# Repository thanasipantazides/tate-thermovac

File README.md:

# Tate 220 ThermoVac Chamber

Here lies a PCB design and code for instrumentation of the UMN Tate Hall rm 220 thermal-vacuum chamber.

The PCB design is in KiCad 10 format. There may be some custom footprint and symbol libraries missing from this distribution; I need to figure out how to bundle all this into the repository.

This board is supposed to read out ~17 NTC thermistors in the chamber, digitize them, and do something useful with the values. It also exposes some general-purpose ADC channels, an SPI, and a UART for peripheral communication. In addition to USB and Ethernet.

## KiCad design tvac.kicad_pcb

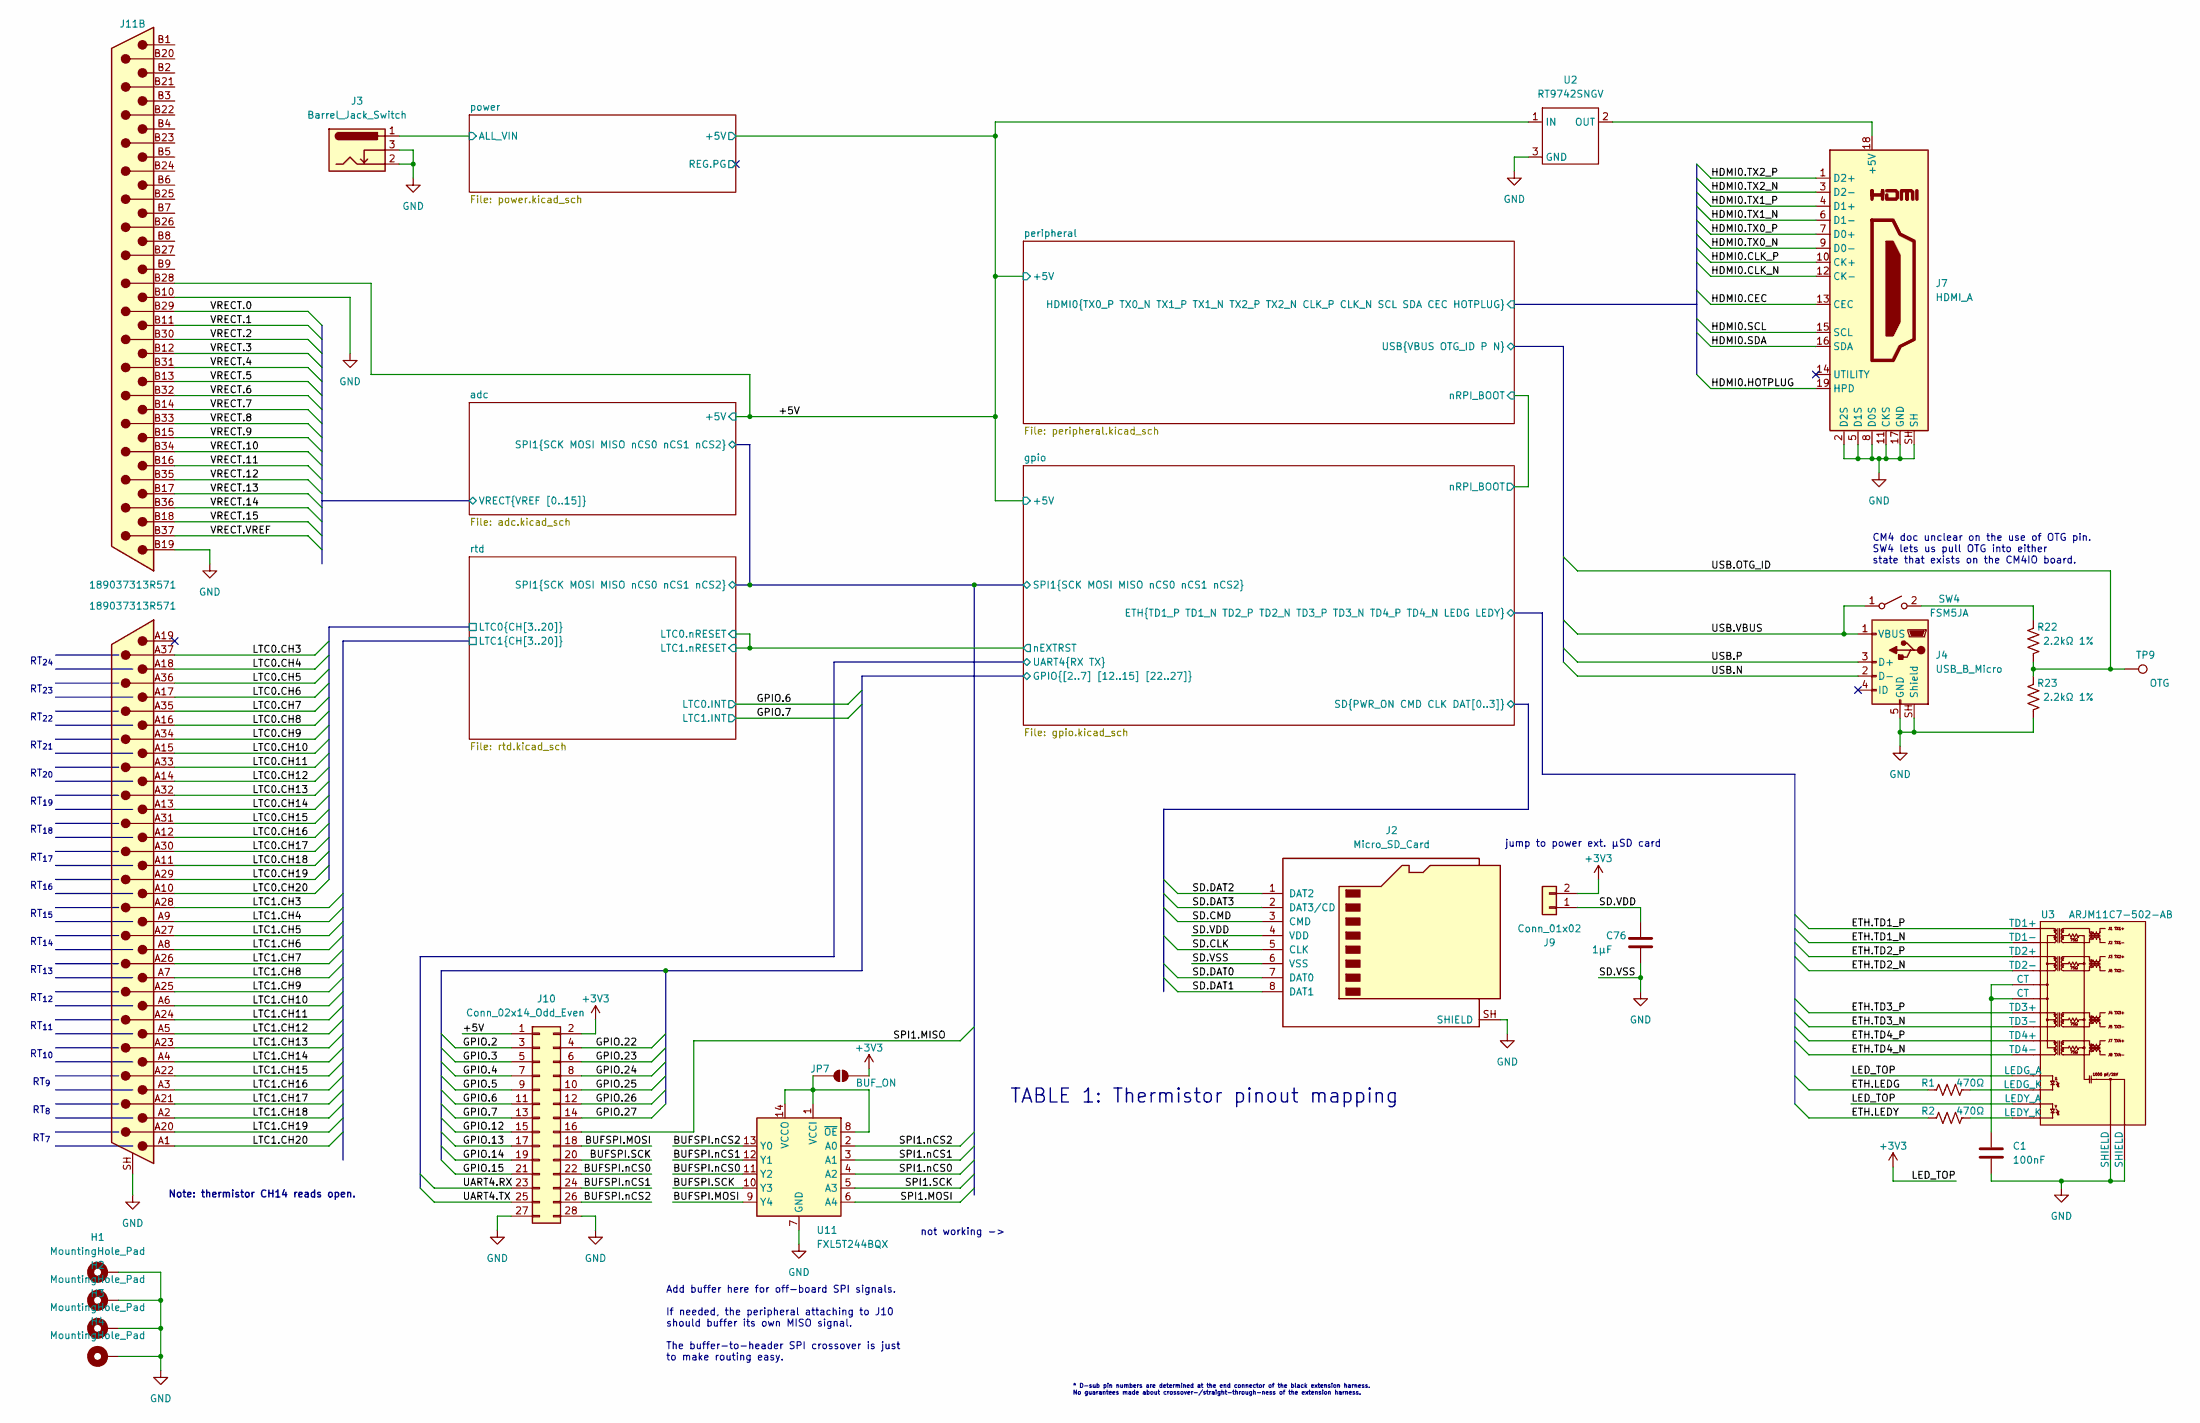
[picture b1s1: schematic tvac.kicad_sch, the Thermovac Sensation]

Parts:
C1: 100nF; C_0603_1608Metric
C76: 1µF; C_0603_1608Metric
H1, H2, H3, H4: MountingHole_Pad; MountingHole_4.3mm_M4_DIN965_Pad
J2: Micro_SD_Card; microSD_HC_Wuerth_693072010801
J3: Barrel_Jack_Switch; BarrelJack_Wuerth_6941xx301002; Digikey 732-5930-ND
J4: USB_B_Micro; USB_Micro-B_Amphenol_10118194-0001LF_Horizontal; Digikey 609-4618-1-ND
J7: HDMI_A; HDMI_A_Amphenol_10029449-x01xLF_Horizontal; Digikey 609-1010-1-ND
J9: Conn_01x02; PinHeader_1x02_P2.54mm_Vertical
J10: Conn_02x14_Odd_Even; PinHeader_2x14_P2.54mm_Vertical
J11: 189037313R571; DSUB-37-Stacked_NorComp-189037313R571
JP7: BUF_ON; SolderJumper-2_P1.3mm_Open_RoundedPad1.0x1.5mm
R1, R2: 470Ω; R_0603_1608Metric
R22, R23: 2.2kΩ 1%; R_0603_1608Metric
SW4: FSM5JA; SW_DIP_SPSTx01_Slide_9.78x4.72mm_W7.62mm_P2.54mm
TP9: OTG; TestPoint_Pad_D2.5mm
U2: RT9742SNGV; SOT-23-3
U3: ARJM11C7-502-AB; RJ45_Abracon_ARJM11C7-502-AB
U11: FXL5T244BQX; DHWQFN-14-1EP_2.5x3mm_P0.5mm_EP1x1.5mm

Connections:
+3V3: J9.2, J10.2, JP7.2 (B), U3.P11 (LEDG_A), U3.P13 (LEDY_A); also elsewhere on the board
/+5V: J10.1, J11.B28 (28), U2.1 (IN); also elsewhere on the board
/BUFSPI.MOSI: J10.18, U11.9 (Y4)
/BUFSPI.SCK: J10.20, U11.10 (Y3)
/BUFSPI.nCS0: J10.22, U11.11 (Y2)
/BUFSPI.nCS1: J10.24, U11.12 (Y1)
/BUFSPI.nCS2: J10.26, U11.13 (Y0)
/SD.VDD: C76.1, J2.4 (VDD), J9.1
/adc/SPI1.MISO: J10.16; also elsewhere on the board
/adc/SPI1.MOSI: U11.6 (A4); also elsewhere on the board
/adc/SPI1.SCK: U11.5 (A3); also elsewhere on the board
/adc/SPI1.nCS0: U11.4 (A2); also elsewhere on the board
/adc/SPI1.nCS1: U11.3 (A1); also elsewhere on the board
/adc/SPI1.nCS2: U11.2 (A0); also elsewhere on the board
/adc/VRECT.0: J11.B29 (29); also elsewhere on the board
/adc/VRECT.1: J11.B11 (11); also elsewhere on the board
/adc/VRECT.2: J11.B30 (30); also elsewhere on the board
/adc/VRECT.3: J11.B12 (12); also elsewhere on the board
/adc/VRECT.4: J11.B31 (31); also elsewhere on the board
/adc/VRECT.5: J11.B13 (13); also elsewhere on the board
/adc/VRECT.6: J11.B32 (32); also elsewhere on the board
/adc/VRECT.7: J11.B14 (14); also elsewhere on the board
/adc/VRECT.8: J11.B33 (33); also elsewhere on the board
/adc/VRECT.9: J11.B15 (15); also elsewhere on the board
/adc/VRECT.10: J11.B34 (34); also elsewhere on the board
/adc/VRECT.11: J11.B16 (16); also elsewhere on the board
/adc/VRECT.12: J11.B35 (35); also elsewhere on the board
/adc/VRECT.13: J11.B17 (17); also elsewhere on the board
/adc/VRECT.14: J11.B36 (36); also elsewhere on the board
/adc/VRECT.15: J11.B18 (18); also elsewhere on the board
/adc/VRECT.VREF: J11.B37 (37); also elsewhere on the board
/gpio/ETH.LEDG: R1.1; also elsewhere on the board
/gpio/ETH.LEDY: R2.1; also elsewhere on the board
/gpio/ETH.TD1_N: U3.P2 (TD1-); also elsewhere on the board
/gpio/ETH.TD1_P: U3.P1 (TD1+); also elsewhere on the board
/gpio/ETH.TD2_N: U3.P4 (TD2-); also elsewhere on the board
/gpio/ETH.TD2_P: U3.P3 (TD2+); also elsewhere on the board
/gpio/ETH.TD3_N: U3.P8 (TD3-); also elsewhere on the board
/gpio/ETH.TD3_P: U3.P7 (TD3+); also elsewhere on the board
/gpio/ETH.TD4_N: U3.P10 (TD4-); also elsewhere on the board
/gpio/ETH.TD4_P: U3.P9 (TD4+); also elsewhere on the board
/gpio/GPIO.2: J10.3; also elsewhere on the board
/gpio/GPIO.3: J10.5; also elsewhere on the board
/gpio/GPIO.4: J10.7; also elsewhere on the board
/gpio/GPIO.5: J10.9; also elsewhere on the board
/gpio/GPIO.6: J10.11; also elsewhere on the board
/gpio/GPIO.7: J10.13; also elsewhere on the board
/gpio/GPIO.12: J10.15; also elsewhere on the board
/gpio/GPIO.13: J10.17; also elsewhere on the board
/gpio/GPIO.14: J10.19; also elsewhere on the board
/gpio/GPIO.15: J10.21; also elsewhere on the board
/gpio/GPIO.22: J10.4; also elsewhere on the board
/gpio/GPIO.23: J10.6; also elsewhere on the board
/gpio/GPIO.24: J10.8; also elsewhere on the board
/gpio/GPIO.25: J10.10; also elsewhere on the board
/gpio/GPIO.26: J10.12; also elsewhere on the board
/gpio/GPIO.27: J10.14; also elsewhere on the board
/gpio/SD.CLK: J2.5 (CLK); also elsewhere on the board
/gpio/SD.CMD: J2.3 (CMD); also elsewhere on the board
/gpio/SD.DAT0: J2.7 (DAT0); also elsewhere on the board
/gpio/SD.DAT1: J2.8 (DAT1); also elsewhere on the board
/gpio/SD.DAT2: J2.1 (DAT2); also elsewhere on the board
/gpio/SD.DAT3: J2.2 (DAT3/CD); also elsewhere on the board
/gpio/UART4.RX: J10.23; also elsewhere on the board
/gpio/UART4.TX: J10.25; also elsewhere on the board
/peripheral/HDMI0.CEC: J7.13 (CEC); also elsewhere on the board
/peripheral/HDMI0.CLK_N: J7.12 (CK-); also elsewhere on the board
/peripheral/HDMI0.CLK_P: J7.10 (CK+); also elsewhere on the board
/peripheral/HDMI0.HOTPLUG: J7.19 (HPD); also elsewhere on the board
/peripheral/HDMI0.SCL: J7.15 (SCL); also elsewhere on the board
/peripheral/HDMI0.SDA: J7.16 (SDA); also elsewhere on the board
/peripheral/HDMI0.TX0_N: J7.9 (D0-); also elsewhere on the board
/peripheral/HDMI0.TX0_P: J7.7 (D0+); also elsewhere on the board
/peripheral/HDMI0.TX1_N: J7.6 (D1-); also elsewhere on the board
/peripheral/HDMI0.TX1_P: J7.4 (D1+); also elsewhere on the board
/peripheral/HDMI0.TX2_N: J7.3 (D2-); also elsewhere on the board
/peripheral/HDMI0.TX2_P: J7.1 (D2+); also elsewhere on the board
/peripheral/USB.N: J4.2 (D-); also elsewhere on the board
/peripheral/USB.OTG_ID: R22.2, R23.1, TP9.1 (1_1); also elsewhere on the board
/peripheral/USB.P: J4.3 (D+); also elsewhere on the board
/peripheral/USB.VBUS: J4.1 (VBUS), SW4.1 (A); also elsewhere on the board
/power/ALL_VIN: J3.1; also elsewhere on the board
/rtd/LTC0.CH4: J11.A18 (18); also elsewhere on the board
/rtd/LTC0.CH6: J11.A17 (17); also elsewhere on the board
/rtd/LTC0.CH8: J11.A16 (16); also elsewhere on the board
/rtd/LTC0.CH9: J11.A29 (29), J11.A30 (30), J11.A31 (31), J11.A32 (32), J11.A33 (33), J11.A34 (34), J11.A35 (35), J11.A36 (36), J11.A37 (37); also elsewhere on the board
/rtd/LTC0.CH10: J11.A15 (15); also elsewhere on the board
/rtd/LTC0.CH12: J11.A14 (14); also elsewhere on the board
/rtd/LTC0.CH14: J11.A13 (13); also elsewhere on the board
/rtd/LTC0.CH16: J11.A12 (12); also elsewhere on the board
/rtd/LTC0.CH18: J11.A11 (11); also elsewhere on the board
/rtd/LTC0.CH20: J11.A10 (10); also elsewhere on the board
/rtd/LTC1.CH4: J11.A9 (9); also elsewhere on the board
/rtd/LTC1.CH6: J11.A8 (8); also elsewhere on the board
/rtd/LTC1.CH8: J11.A7 (7); also elsewhere on the board
/rtd/LTC1.CH9: J11.A20 (20), J11.A21 (21), J11.A22 (22), J11.A23 (23), J11.A24 (24), J11.A25 (25), J11.A26 (26), J11.A27 (27), J11.A28 (28); also elsewhere on the board
/rtd/LTC1.CH10: J11.A6 (6); also elsewhere on the board
/rtd/LTC1.CH12: J11.A5 (5); also elsewhere on the board
/rtd/LTC1.CH14: J11.A4 (4); also elsewhere on the board
/rtd/LTC1.CH16: J11.A3 (3); also elsewhere on the board
/rtd/LTC1.CH18: J11.A2 (2); also elsewhere on the board
/rtd/LTC1.CH20: J11.A1 (1); also elsewhere on the board
GND: C1.2, C76.2, H1.1 (1_1), H2.1 (1_1), H3.1 (1_1), H4.1 (1_1), J2.6 (VSS), J2.SH (SHIELD), J3.2, J3.3, J4.5 (GND), J4.SH (Shield), J7.2 (D2S), J7.5 (D1S), J7.8 (D0S), J7.11 (CKS), J7.17 (GND), J7.SH, J10.27, J10.28, J11.B10 (10), J11.B19 (19), J11.SH (PAD), R23.2, U2.3 (GND), U3.H1 (SHIELD), U3.H2 (SHIELD), U11.7 (GND); also elsewhere on the board
unnamed: C1.1, U3.P5 (CT), U3.P6 (CT)
unnamed: J7.18 (+5V), U2.2 (OUT)
unnamed: JP7.1 (A), U11.1 (VCCI), U11.8 (~OE), U11.14 (VCCO)
unnamed: R22.1, SW4.2 (B)
unnamed: R1.2, U3.P12 (LEDG_K)
unnamed: R2.2, U3.P14 (LEDY_K)

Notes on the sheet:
RT_{8}
RT_{23}
jump to power ext. µSD card
RT_{12}
RT_{24}
RT_{17}
Note: thermistor CH14 reads open.
RT_{16}
RT_{11}
RT_{7}
RT_{20}
RT_{22}
TABLE 1: Thermistor pinout mapping
RT_{9}
RT_{13}
RT_{21}
RT_{19}
not working ->
* D-sub pin numbers are determined at the end connector of the black extension harness. No guarantees made about crossover-/straight-through-ness of the extension harness.
Add buffer here for off-board SPI signals. If needed, the peripheral attaching to J10 should buffer its own MISO signal. The buffer-to-header SPI crossover is just to make routing easy.
RT_{14}
RT_{18}
RT_{15}
CM4 doc unclear on the use of OTG pin. SW4 lets us pull OTG into either state that exists on the CM4IO board.
RT_{10}

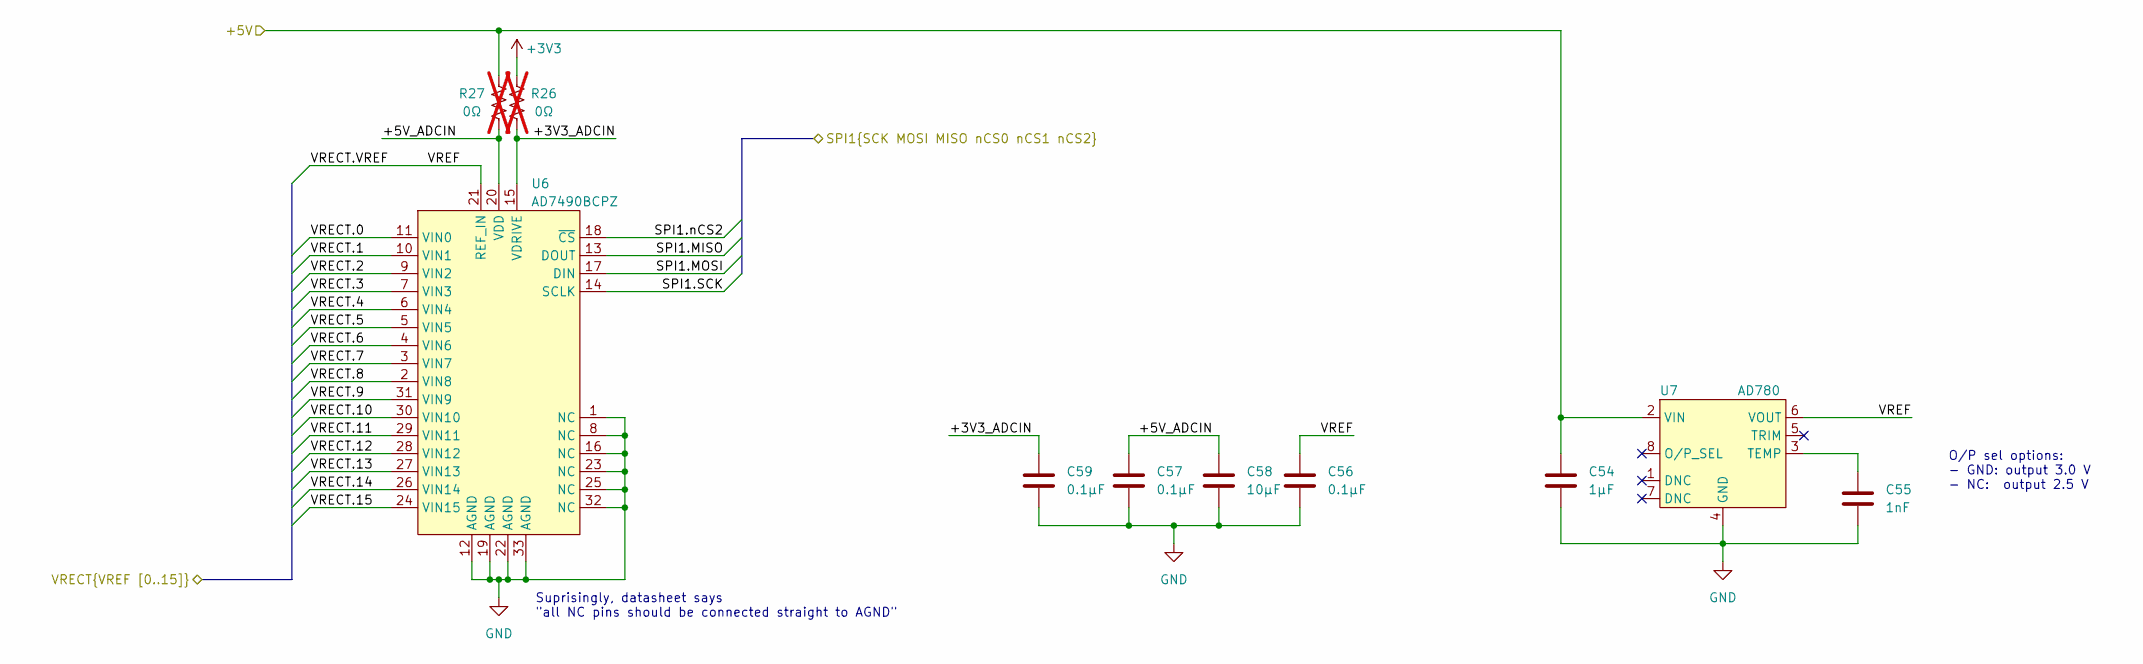
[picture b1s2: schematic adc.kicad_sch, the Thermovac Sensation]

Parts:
C54: 1µF; C_0603_1608Metric
C55: 1nF; C_0603_1608Metric
C56, C57, C59: 0.1µF; C_0603_1608Metric
C58: 10µF; C_1210_3225Metric
R26, R27: 0Ω; R_1210_3225Metric; not fitted
U6: AD7490BCPZ; LFCSP-32-1EP_5x5mm_P0.5mm_EP3.5x3.5mm; Digikey 505-AD7490BCPZ-ND
U7: AD780; SOIC-8_3.9x4.9mm_P1.27mm; Digikey 505-AD780ARZ-ND

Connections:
+3V3: R26.2; also elsewhere on the board
/+5V: C54.1, R27.2, U7.2 (VIN); also elsewhere on the board
/adc/+3V3_ADCIN: C59.1, R26.1, U6.15 (VDRIVE)
/adc/+5V_ADCIN: C57.1, C58.1, R27.1, U6.20 (VDD)
/adc/SPI1.MISO: U6.13 (DOUT); also elsewhere on the board
/adc/SPI1.MOSI: U6.17 (DIN); also elsewhere on the board
/adc/SPI1.SCK: U6.14 (SCLK); also elsewhere on the board
/adc/SPI1.nCS2: U6.18 (~CS); also elsewhere on the board
/adc/VRECT.0: U6.11 (VIN0); also elsewhere on the board
/adc/VRECT.1: U6.10 (VIN1); also elsewhere on the board
/adc/VRECT.2: U6.9 (VIN2); also elsewhere on the board
/adc/VRECT.3: U6.7 (VIN3); also elsewhere on the board
/adc/VRECT.4: U6.6 (VIN4); also elsewhere on the board
/adc/VRECT.5: U6.5 (VIN5); also elsewhere on the board
/adc/VRECT.6: U6.4 (VIN6); also elsewhere on the board
/adc/VRECT.7: U6.3 (VIN7); also elsewhere on the board
/adc/VRECT.8: U6.2 (VIN8); also elsewhere on the board
/adc/VRECT.9: U6.31 (VIN9); also elsewhere on the board
/adc/VRECT.10: U6.30 (VIN10); also elsewhere on the board
/adc/VRECT.11: U6.29 (VIN11); also elsewhere on the board
/adc/VRECT.12: U6.28 (VIN12); also elsewhere on the board
/adc/VRECT.13: U6.27 (VIN13); also elsewhere on the board
/adc/VRECT.14: U6.26 (VIN14); also elsewhere on the board
/adc/VRECT.15: U6.24 (VIN15); also elsewhere on the board
/adc/VRECT.VREF: C56.1, U6.21 (REF_IN), U7.6 (VOUT); also elsewhere on the board
GND: C54.2, C55.2, C56.2, C57.2, C58.2, C59.2, U6.1 (NC), U6.8 (NC), U6.12 (AGND), U6.16 (NC), U6.19 (AGND), U6.22 (AGND), U6.23 (NC), U6.25 (NC), U6.32 (NC), U6.33 (AGND), U7.4 (GND); also elsewhere on the board
unnamed: C55.1, U7.3 (TEMP)

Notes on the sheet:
O/P sel options: - GND: output 3.0 V - NC: output 2.5 V
Suprisingly, datasheet says "all NC pins should be connected straight to AGND"

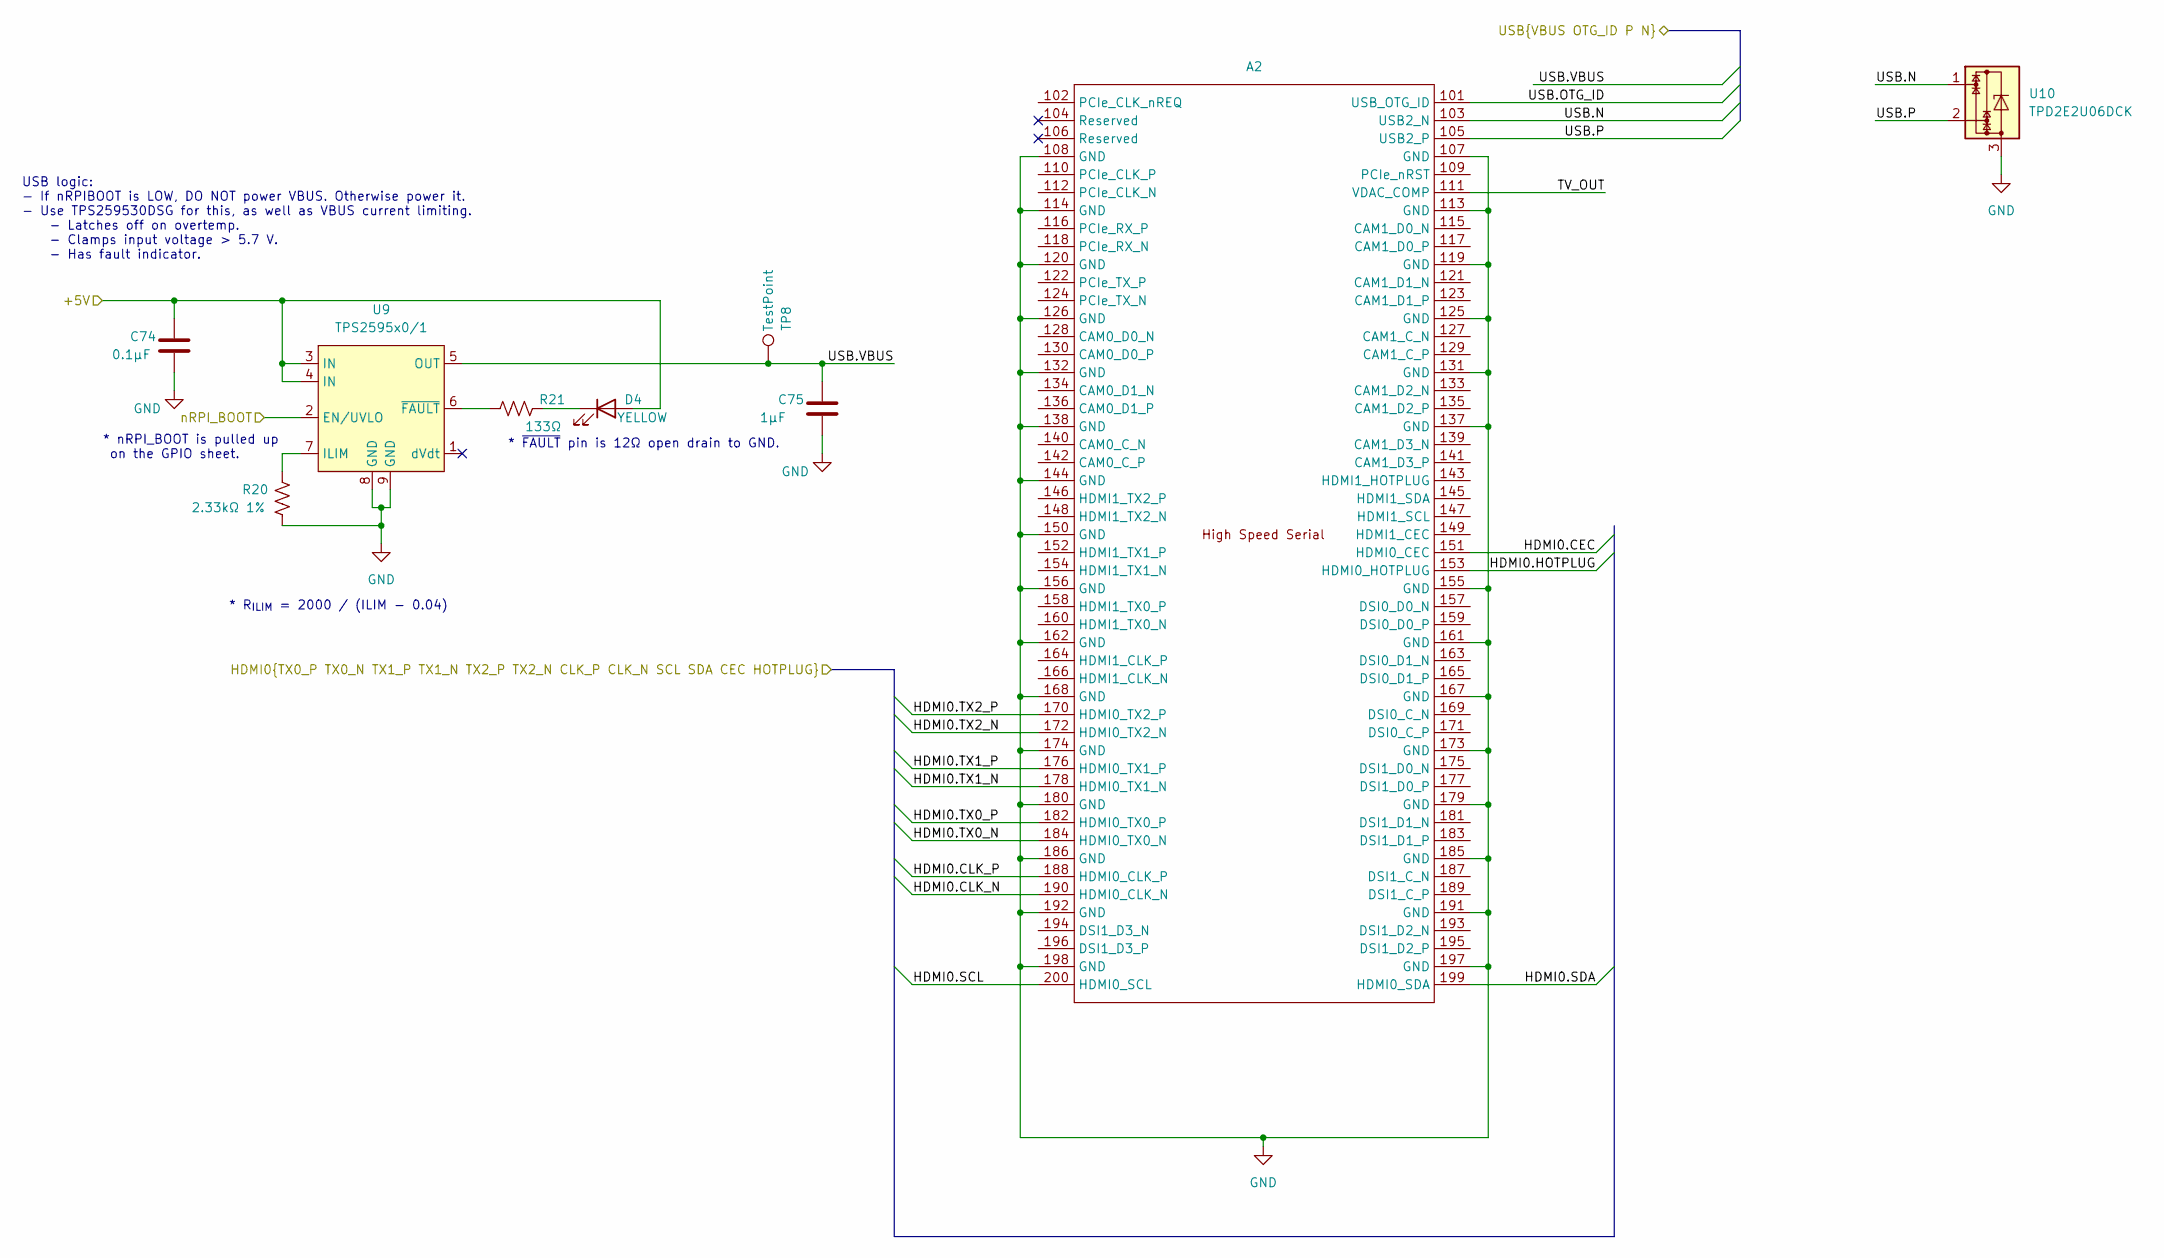
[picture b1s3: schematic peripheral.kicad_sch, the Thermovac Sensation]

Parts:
A2: Hirose_DF40HC(3.0)-100DS-0.4V_2x50_P0.4mm_RPi_CM4-BUS
C74: 0.1µF; C_0603_1608Metric
C75: 1µF; C_0603_1608Metric
D4: YELLOW; LED_1206_3216Metric; Digikey 160-1406-1-ND
R20: 2.33kΩ 1%; R_0603_1608Metric
R21: 133Ω; R_0603_1608Metric
TP8: TestPoint; TestPoint_Pad_D2.5mm
U9: TPS2595x0/1; WSON-8-1EP_2x2mm_P0.5mm_EP0.9x1.6mm
U10: TPD2E2U06DCK; SOT-323_SC-70

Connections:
/+5V: C74.1, D4.2 (A), U9.3 (IN), U9.4 (IN); also elsewhere on the board
/gpio/nRPI_BOOT: U9.2 (EN/UVLO); also elsewhere on the board
/peripheral/HDMI0.CEC: A2.151 (HDMI0_CEC); also elsewhere on the board
/peripheral/HDMI0.CLK_N: A2.190 (HDMI0_CLK_N); also elsewhere on the board
/peripheral/HDMI0.CLK_P: A2.188 (HDMI0_CLK_P); also elsewhere on the board
/peripheral/HDMI0.HOTPLUG: A2.153 (HDMI0_HOTPLUG); also elsewhere on the board
/peripheral/HDMI0.SCL: A2.200 (HDMI0_SCL); also elsewhere on the board
/peripheral/HDMI0.SDA: A2.199 (HDMI0_SDA); also elsewhere on the board
/peripheral/HDMI0.TX0_N: A2.184 (HDMI0_TX0_N); also elsewhere on the board
/peripheral/HDMI0.TX0_P: A2.182 (HDMI0_TX0_P); also elsewhere on the board
/peripheral/HDMI0.TX1_N: A2.178 (HDMI0_TX1_N); also elsewhere on the board
/peripheral/HDMI0.TX1_P: A2.176 (HDMI0_TX1_P); also elsewhere on the board
/peripheral/HDMI0.TX2_N: A2.172 (HDMI0_TX2_N); also elsewhere on the board
/peripheral/HDMI0.TX2_P: A2.170 (HDMI0_TX2_P); also elsewhere on the board
/peripheral/TV_OUT: A2.111 (VDAC_COMP)
/peripheral/USB.N: A2.103 (USB2_N), U10.1; also elsewhere on the board
/peripheral/USB.OTG_ID: A2.101 (USB_OTG_ID); also elsewhere on the board
/peripheral/USB.P: A2.105 (USB2_P), U10.2; also elsewhere on the board
/peripheral/USB.VBUS: C75.1, TP8.1 (1_1), U9.5 (OUT); also elsewhere on the board
GND: A2.107 (GND), A2.108 (GND), A2.113 (GND), A2.114 (GND), A2.119 (GND), A2.120 (GND), A2.125 (GND), A2.126 (GND), A2.131 (GND), A2.132 (GND), A2.137 (GND), A2.138 (GND), A2.144 (GND), A2.150 (GND), A2.155 (GND), A2.156 (GND), A2.161 (GND), A2.162 (GND), A2.167 (GND), A2.168 (GND), A2.173 (GND), A2.174 (GND), A2.179 (GND), A2.180 (GND), A2.185 (GND), A2.186 (GND), A2.191 (GND), A2.192 (GND), A2.197 (GND), A2.198 (GND), C74.2, C75.2, R20.1, U9.8 (GND), U9.9 (GND), U10.3; also elsewhere on the board
unnamed: D4.1 (K), R21.1
unnamed: R20.2, U9.7 (ILIM)
unnamed: R21.2, U9.6 (~FAULT)

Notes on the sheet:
USB logic: - If nRPIBOOT is LOW, DO NOT power VBUS. Otherwise power it. - Use TPS259530DSG for this, as well as VBUS current limiting. - Latches off on overtemp. - Clamps input voltage > 5.7 V. - Has fault indicator.
* R_{ILIM} = 2000 / (ILIM - 0.04)
* nRPI_BOOT is pulled up on the GPIO sheet.
* ~{FAULT} pin is 12Ω open drain to GND.

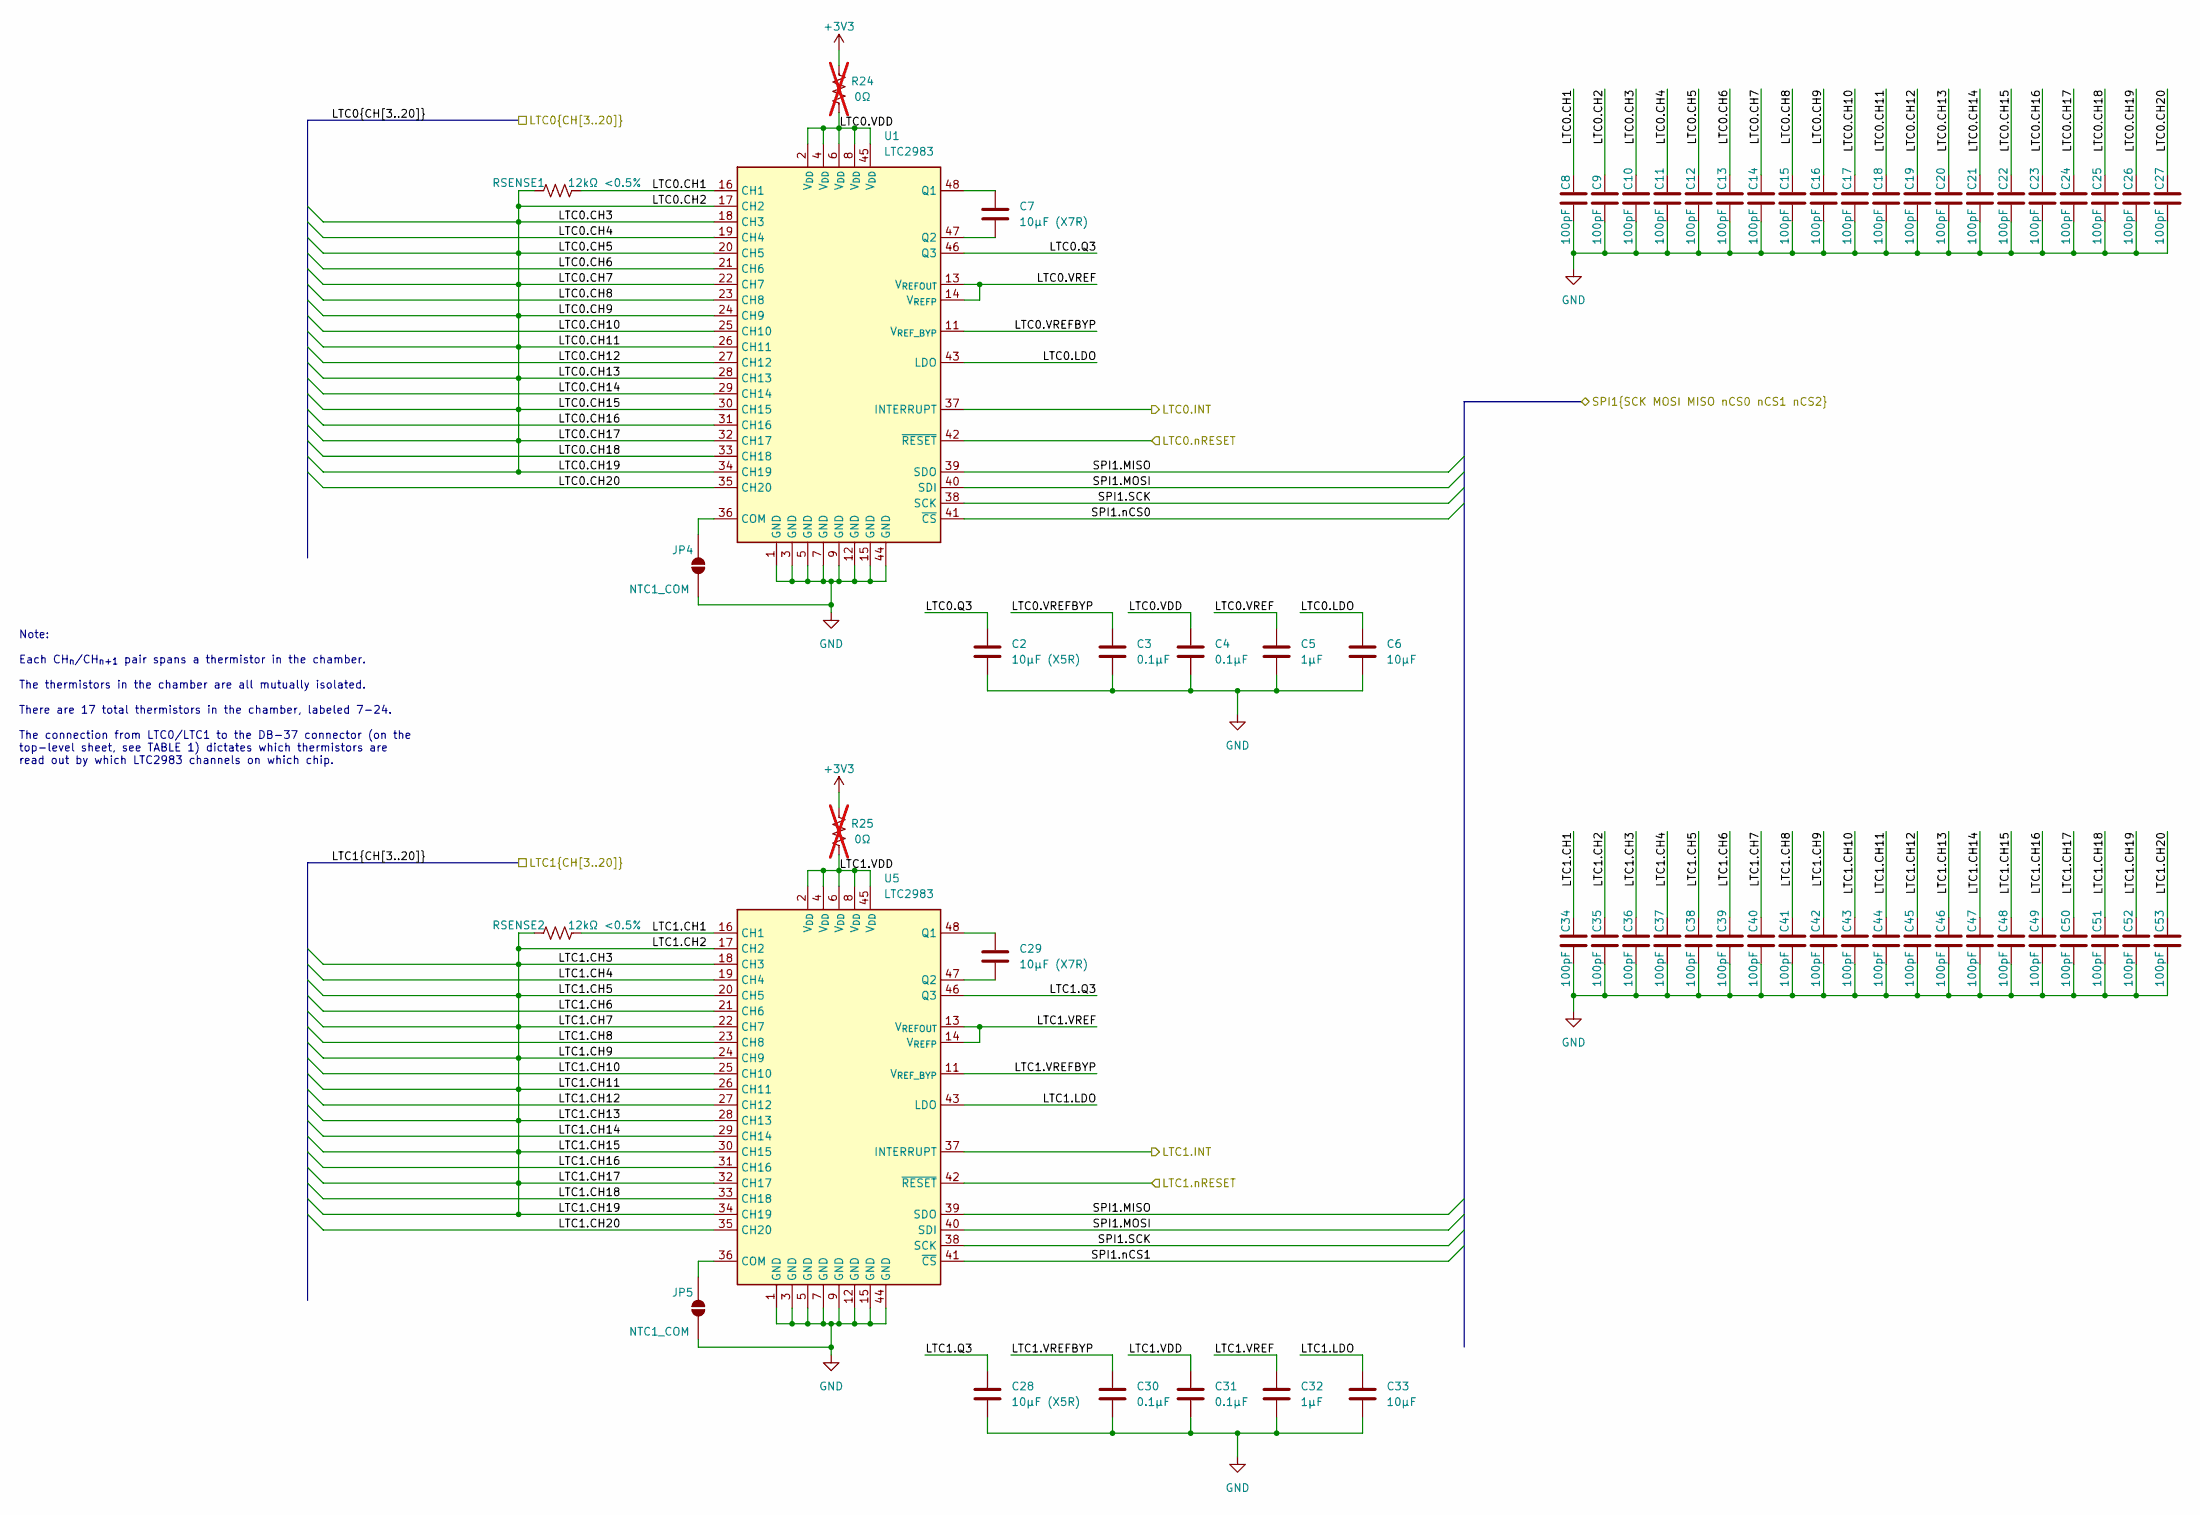
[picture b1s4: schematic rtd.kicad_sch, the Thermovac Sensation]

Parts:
C2, C28: 10µF (X5R); C_1210_3225Metric
C3, C4, C30, C31: 0.1µF; C_0603_1608Metric
C5, C32: 1µF; C_0603_1608Metric
C6, C33: 10µF; C_1210_3225Metric
C7, C29: 10µF (X7R); C_1210_3225Metric
C8, C9, C10, C11, C12, C13, C14, C15, C16, C17, C18, C19, C20, C21, C22, C23, C24, C25, C26, C27, C34, C35, C36, C37, C38, C39, C40, C41, C42, C43, C44, C45, C46, C47, C48, C49, C50, C51, C52, C53: 100pF; C_0603_1608Metric
JP4, JP5: NTC1_COM; SolderJumper-2_P1.3mm_Open_RoundedPad1.0x1.5mm
R24, R25: 0Ω; R_1210_3225Metric; not fitted
RSENSE1, RSENSE2: 12kΩ <0.5%; R_0603_1608Metric
U1, U5: LTC2983; LQFP-48_7x7mm_P0.5mm

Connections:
+3V3: R24.2, R25.2; also elsewhere on the board
/adc/SPI1.MISO: U1.39 (SDO), U5.39 (SDO); also elsewhere on the board
/adc/SPI1.MOSI: U1.40 (SDI), U5.40 (SDI); also elsewhere on the board
/adc/SPI1.SCK: U1.38 (SCK), U5.38 (SCK); also elsewhere on the board
/adc/SPI1.nCS0: U1.41 (~CS); also elsewhere on the board
/adc/SPI1.nCS1: U5.41 (~CS); also elsewhere on the board
/gpio/GPIO.6: U1.37 (INTERRUPT); also elsewhere on the board
/gpio/GPIO.7: U5.37 (INTERRUPT); also elsewhere on the board
/gpio/nEXTRST: U1.42 (~RESET), U5.42 (~RESET); also elsewhere on the board
/rtd/LTC0.CH1: C8.1, RSENSE1.2, U1.16 (CH1)
/rtd/LTC0.CH4: C11.1, U1.19 (CH4); also elsewhere on the board
/rtd/LTC0.CH6: C13.1, U1.21 (CH6); also elsewhere on the board
/rtd/LTC0.CH8: C15.1, U1.23 (CH8); also elsewhere on the board
/rtd/LTC0.CH9: C9.1, C10.1, C12.1, C14.1, C16.1, C18.1, C20.1, C22.1, C24.1, C26.1, RSENSE1.1, U1.17 (CH2), U1.18 (CH3), U1.20 (CH5), U1.22 (CH7), U1.24 (CH9), U1.26 (CH11), U1.28 (CH13), U1.30 (CH15), U1.32 (CH17), U1.34 (CH19); also elsewhere on the board
/rtd/LTC0.CH10: C17.1, U1.25 (CH10); also elsewhere on the board
/rtd/LTC0.CH12: C19.1, U1.27 (CH12); also elsewhere on the board
/rtd/LTC0.CH14: C21.1, U1.29 (CH14); also elsewhere on the board
/rtd/LTC0.CH16: C23.1, U1.31 (CH16); also elsewhere on the board
/rtd/LTC0.CH18: C25.1, U1.33 (CH18); also elsewhere on the board
/rtd/LTC0.CH20: C27.1, U1.35 (CH20); also elsewhere on the board
/rtd/LTC0.LDO: C6.1, U1.43 (LDO)
/rtd/LTC0.Q3: C2.1, U1.46 (Q3)
/rtd/LTC0.VDD: C4.1, R24.1, U1.2 (V_{DD}), U1.4 (V_{DD}), U1.6 (V_{DD}), U1.8 (V_{DD}), U1.45 (V_{DD})
/rtd/LTC0.VREF: C5.1, U1.13 (V_{REFOUT}), U1.14 (V_{REFP})
/rtd/LTC0.VREFBYP: C3.1, U1.11 (V_{REF_BYP})
/rtd/LTC1.CH1: C34.1, RSENSE2.2, U5.16 (CH1)
/rtd/LTC1.CH4: C37.1, U5.19 (CH4); also elsewhere on the board
/rtd/LTC1.CH6: C39.1, U5.21 (CH6); also elsewhere on the board
/rtd/LTC1.CH8: C41.1, U5.23 (CH8); also elsewhere on the board
/rtd/LTC1.CH9: C35.1, C36.1, C38.1, C40.1, C42.1, C44.1, C46.1, C48.1, C50.1, C52.1, RSENSE2.1, U5.17 (CH2), U5.18 (CH3), U5.20 (CH5), U5.22 (CH7), U5.24 (CH9), U5.26 (CH11), U5.28 (CH13), U5.30 (CH15), U5.32 (CH17), U5.34 (CH19); also elsewhere on the board
/rtd/LTC1.CH10: C43.1, U5.25 (CH10); also elsewhere on the board
/rtd/LTC1.CH12: C45.1, U5.27 (CH12); also elsewhere on the board
/rtd/LTC1.CH14: C47.1, U5.29 (CH14); also elsewhere on the board
/rtd/LTC1.CH16: C49.1, U5.31 (CH16); also elsewhere on the board
/rtd/LTC1.CH18: C51.1, U5.33 (CH18); also elsewhere on the board
/rtd/LTC1.CH20: C53.1, U5.35 (CH20); also elsewhere on the board
/rtd/LTC1.LDO: C33.1, U5.43 (LDO)
/rtd/LTC1.Q3: C28.1, U5.46 (Q3)
/rtd/LTC1.VDD: C31.1, R25.1, U5.2 (V_{DD}), U5.4 (V_{DD}), U5.6 (V_{DD}), U5.8 (V_{DD}), U5.45 (V_{DD})
/rtd/LTC1.VREF: C32.1, U5.13 (V_{REFOUT}), U5.14 (V_{REFP})
/rtd/LTC1.VREFBYP: C30.1, U5.11 (V_{REF_BYP})
GND: C2.2, C3.2, C4.2, C5.2, C6.2, C8.2, C9.2, C10.2, C11.2, C12.2, C13.2, C14.2, C15.2, C16.2, C17.2, C18.2, C19.2, C20.2, C21.2, C22.2, C23.2, C24.2, C25.2, C26.2, C27.2, C28.2, C30.2, C31.2, C32.2, C33.2, C34.2, C35.2, C36.2, C37.2, C38.2, C39.2, C40.2, C41.2, C42.2, C43.2, C44.2, C45.2, C46.2, C47.2, C48.2, C49.2, C50.2, C51.2, C52.2, C53.2, JP4.2 (B), JP5.2 (B), U1.1 (GND), U1.3 (GND), U1.5 (GND), U1.7 (GND), U1.9 (GND), U1.12 (GND), U1.15 (GND), U1.44 (GND), U5.1 (GND), U5.3 (GND), U5.5 (GND), U5.7 (GND), U5.9 (GND), U5.12 (GND), U5.15 (GND), U5.44 (GND); also elsewhere on the board
unnamed: JP4.1 (A), U1.36 (COM)
unnamed: JP5.1 (A), U5.36 (COM)
unnamed: C7.1, U1.48 (Q1)
unnamed: C7.2, U1.47 (Q2)
unnamed: C29.1, U5.48 (Q1)
unnamed: C29.2, U5.47 (Q2)

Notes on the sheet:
Note: Each CH_{n}/CH_{n+1} pair spans a thermistor in the chamber. The thermistors in the chamber are all mutually isolated. There are 17 total thermistors in the chamber, labeled 7-24. The connection from LTC0/LTC1 to the DB-37 connector (on the top-level sheet, see TABLE 1) dictates which thermis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
